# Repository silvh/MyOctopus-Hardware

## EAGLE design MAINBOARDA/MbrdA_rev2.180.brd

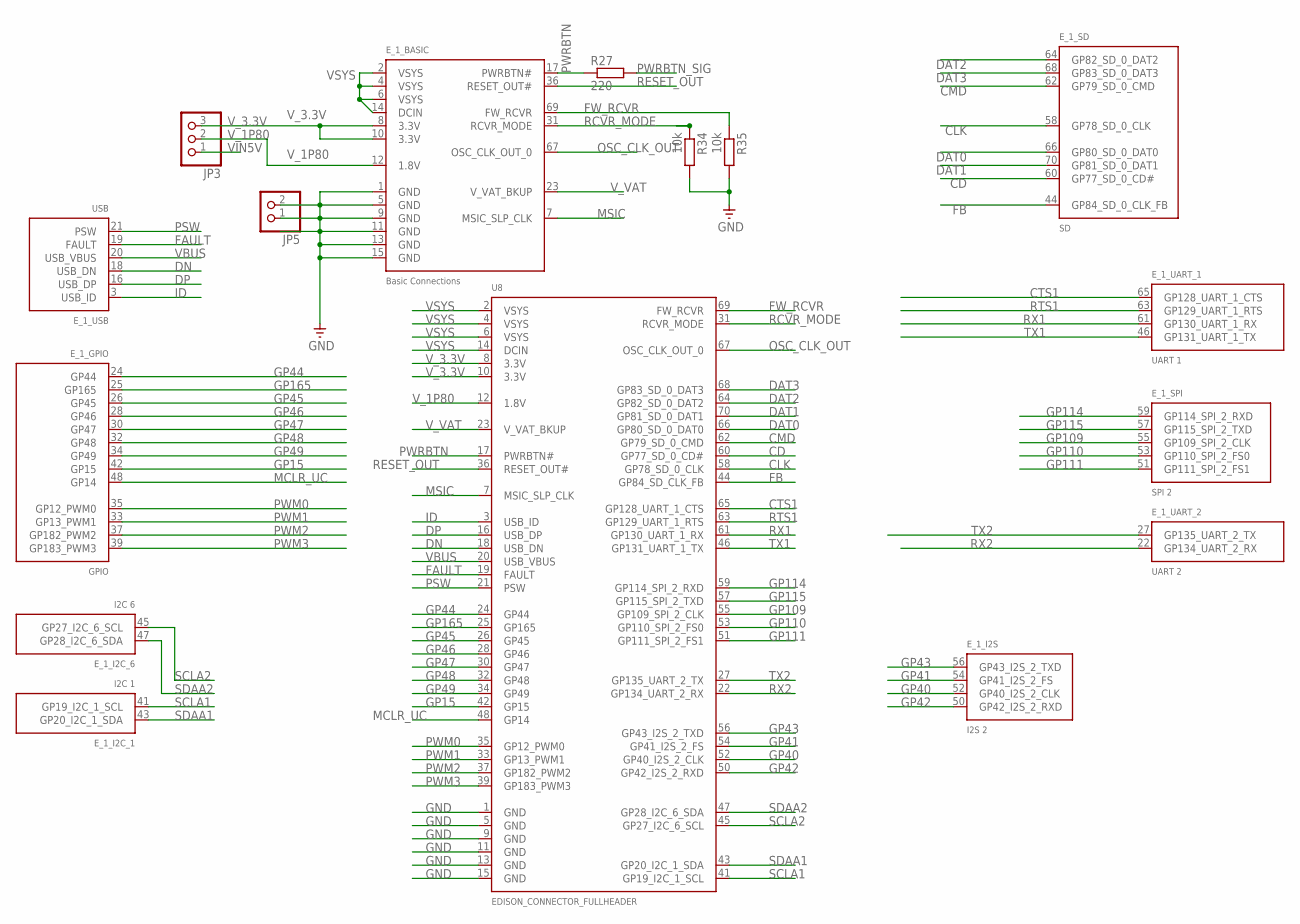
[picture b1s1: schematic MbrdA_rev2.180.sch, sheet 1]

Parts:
E_1: EDISON_CONNECTOR_SEGMENTED; EDISON_DAUGHTER; MOUSER 798-DF40HC3070DS4V51
JP3: PINHD-1X3; 1X03
JP5: PINHD-1X2; 1X02
R27: 220; R0201
R34, R35: 10k; R0201
U8: EDISON_CONNECTOR_FULLHEADER; DF40C-70DP-0.4(51)

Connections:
CD: E_1.60 (GP77_SD_0_CD#), U8.60 (GP77_SD_0_CD#); also elsewhere on the board
CLK: E_1.58 (GP78_SD_0_CLK), U8.58 (GP78_SD_0_CLK); also elsewhere on the board
CMD: E_1.62 (GP79_SD_0_CMD), U8.62 (GP79_SD_0_CMD); also elsewhere on the board
CTS1: E_1.65 (GP128_UART_1_CTS), U8.65 (GP128_UART_1_CTS); also elsewhere on the board
DAT0: E_1.66 (GP80_SD_0_DAT0), U8.66 (GP80_SD_0_DAT0); also elsewhere on the board
DAT1: E_1.70 (GP81_SD_0_DAT1), U8.70 (GP81_SD_0_DAT1); also elsewhere on the board
DAT2: E_1.64 (GP82_SD_0_DAT2), U8.64 (GP82_SD_0_DAT2); also elsewhere on the board
DAT3: E_1.68 (GP83_SD_0_DAT3), U8.68 (GP83_SD_0_DAT3); also elsewhere on the board
DN: E_1.18 (USB_DN), U8.18 (USB_DN); also elsewhere on the board
DP: E_1.16 (USB_DP), U8.16 (USB_DP); also elsewhere on the board
FAULT: E_1.19 (FAULT), U8.19 (FAULT); also elsewhere on the board
FB: E_1.44 (GP84_SD_0_CLK_FB), U8.44 (GP84_SD_CLK_FB); also elsewhere on the board
FW_RCVR: E_1.69 (FW_RCVR), R35.1, U8.69 (FW_RCVR); also elsewhere on the board
GND: E_1.1 (GND), E_1.5 (GND), E_1.9 (GND), E_1.11 (GND), E_1.13 (GND), E_1.15 (GND), JP5.1, JP5.2, R34.2, R35.2, U8.1 (GND), U8.5 (GND), U8.9 (GND), U8.11 (GND), U8.13 (GND), U8.15 (GND); also elsewhere on the board
GP15: E_1.42 (GP15), U8.42 (GP15)
GP40: E_1.52 (GP40_I2S_2_CLK), U8.52 (GP40_I2S_2_CLK)
GP41: E_1.54 (GP41_I2S_2_FS), U8.54 (GP41_I2S_2_FS)
GP42: E_1.50 (GP42_I2S_2_RXD), U8.50 (GP42_I2S_2_RXD)
GP43: E_1.56 (GP43_I2S_2_TXD), U8.56 (GP43_I2S_2_TXD)
GP44: E_1.24 (GP44), U8.24 (GP44); also elsewhere on the board
GP45: E_1.26 (GP45), U8.26 (GP45); also elsewhere on the board
GP46: E_1.28 (GP46), U8.28 (GP46); also elsewhere on the board
GP47: E_1.30 (GP47), U8.30 (GP47)
GP48: E_1.32 (GP48), U8.32 (GP48); also elsewhere on the board
GP49: E_1.34 (GP49), U8.34 (GP49); also elsewhere on the board
GP109: E_1.55 (GP109_SPI_2_CLK), U8.55 (GP109_SPI_2_CLK)
GP110: E_1.53 (GP110_SPI_2_FS0), U8.53 (GP110_SPI_2_FS0)
GP111: E_1.51 (GP111_SPI_2_FS1), U8.51 (GP111_SPI_2_FS1)
GP114: E_1.59 (GP114_SPI_2_RXD), U8.59 (GP114_SPI_2_RXD)
GP115: E_1.57 (GP115_SPI_2_TXD), U8.57 (GP115_SPI_2_TXD)
GP165: E_1.25 (GP165), U8.25 (GP165); also elsewhere on the board
ID: E_1.3 (USB_ID), U8.3 (USB_ID); also elsewhere on the board
MCLR_UC: E_1.48 (GP14), U8.48 (GP14); also elsewhere on the board
MSIC: E_1.7 (MSIC_SLP_CLK), U8.7 (MSIC_SLP_CLK)
OSC_CLK_OUT: E_1.67 (OSC_CLK_OUT_0), U8.67 (OSC_CLK_OUT_0)
PSW: E_1.21 (PSW), U8.21 (PSW); also elsewhere on the board
PWM0: E_1.35 (GP12_PWM0), U8.35 (GP12_PWM0); also elsewhere on the board
PWM1: E_1.33 (GP13_PWM1), U8.33 (GP13_PWM1); also elsewhere on the board
PWM2: E_1.37 (GP182_PWM2), U8.37 (GP182_PWM2)
PWM3: E_1.39 (GP183_PWM3), U8.39 (GP183_PWM3)
PWRBTN: E_1.17 (PWRBTN#), R27.1, U8.17 (PWRBTN#)
PWRBTN_SIG: R27.2; also elsewhere on the board
RCVR_MODE: E_1.31 (RCVR_MODE), R34.1, U8.31 (RCVR_MODE); also elsewhere on the board
RESET_OUT: E_1.36 (RESET_OUT#), U8.36 (RESET_OUT#); also elsewhere on the board
RTS1: E_1.63 (GP129_UART_1_RTS), U8.63 (GP129_UART_1_RTS); also elsewhere on the board
RX1: E_1.61 (GP130_UART_1_RX), U8.61 (GP130_UART_1_RX); also elsewhere on the board
RX2: E_1.22 (GP134_UART_2_RX), U8.22 (GP134_UART_2_RX); also elsewhere on the board
SCLA1: E_1.41 (GP19_I2C_1_SCL), U8.41 (GP19_I2C_1_SCL); also elsewhere on the board
SCLA2: E_1.45 (GP27_I2C_6_SCL), U8.45 (GP27_I2C_6_SCL); also elsewhere on the board
SDAA1: E_1.43 (GP20_I2C_1_SDA), U8.43 (GP20_I2C_1_SDA); also elsewhere on the board
SDAA2: E_1.47 (GP28_I2C_6_SDA), U8.47 (GP28_I2C_6_SDA); also elsewhere on the board
TX1: E_1.46 (GP131_UART_1_TX), U8.46 (GP131_UART_1_TX); also elsewhere on the board
TX2: E_1.27 (GP135_UART_2_TX), U8.27 (GP135_UART_2_TX); also elsewhere on the board
VBUS: E_1.20 (USB_VBUS), U8.20 (USB_VBUS); also elsewhere on the board
VIN5V: JP3.1; also elsewhere on the board
VSYS: E_1.2 (VSYS), E_1.4 (VSYS), E_1.6 (VSYS), E_1.14 (DCIN), U8.2 (VSYS), U8.4 (VSYS), U8.6 (VSYS), U8.14 (DCIN); also elsewhere on the board
V_1P80: E_1.12 (1.8V), JP3.2, U8.12 (1.8V); also elsewhere on the board
V_3.3V: E_1.8 (3.3V), E_1.10 (3.3V), JP3.3, U8.8 (3.3V), U8.10 (3.3V); also elsewhere on the board
V_VAT: E_1.23 (V_VAT_BKUP), U8.23 (V_VAT_BKUP)

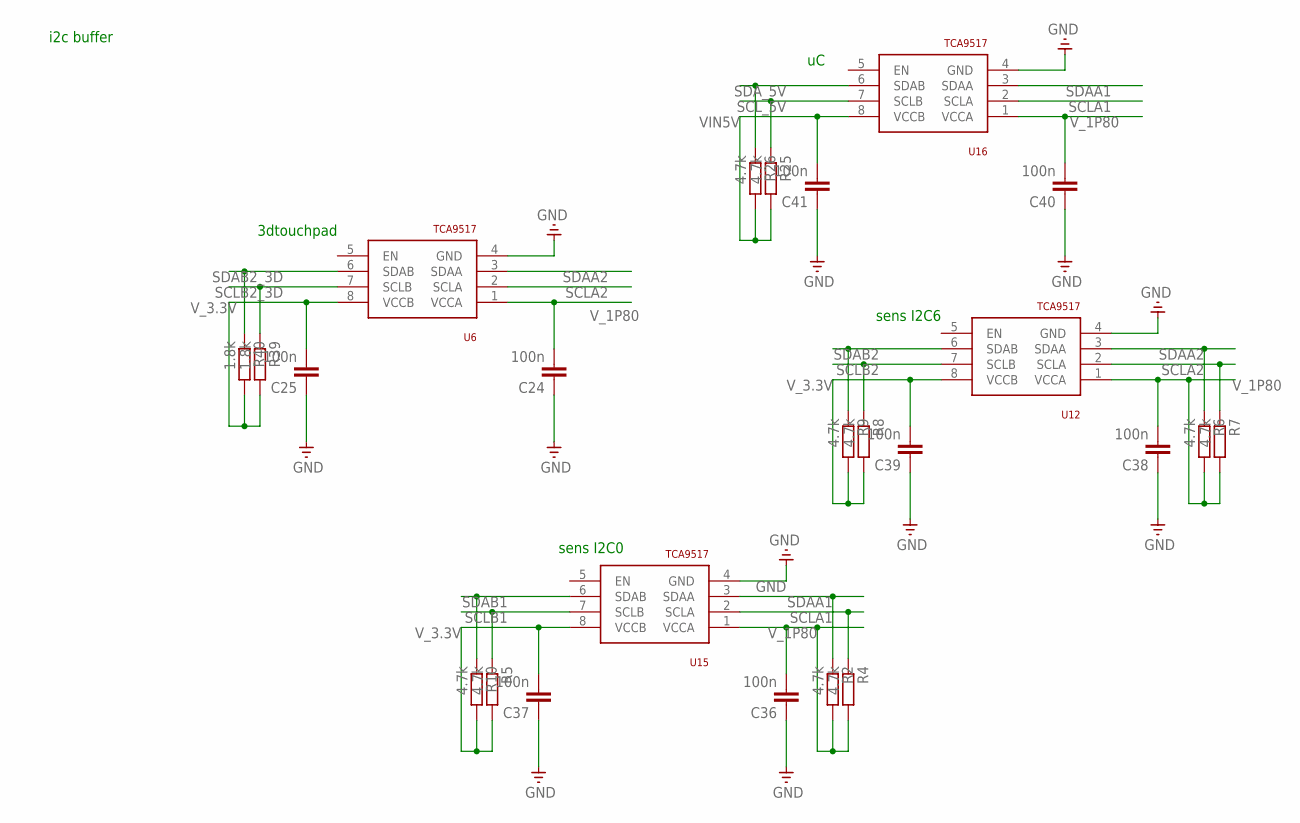
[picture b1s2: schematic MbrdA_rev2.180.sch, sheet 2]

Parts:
C24, C25, C36, C37, C38, C39, C40, C41: 100n; C0201
R2, R4, R5, R6, R7, R8, R9, R10, R25, R26: 4.7k; R0201
R39, R40: 1.8k; R0201
U6, U12, U15, U16: TCA9517; SO-08

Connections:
GND: C24.1, C25.1, C36.1, C37.1, C38.1, C39.1, C40.1, C41.1, U6.4 (GND), U12.4 (GND), U15.4 (GND), U16.4 (GND); also elsewhere on the board
SCLA1: R4.1, U15.2 (SCLA), U16.2 (SCLA); also elsewhere on the board
SCLA2: R7.1, U6.2 (SCLA), U12.2 (SCLA); also elsewhere on the board
SCLB1: R5.1, U15.7 (SCLB); also elsewhere on the board
SCLB2: R8.1, U12.7 (SCLB); also elsewhere on the board
SCLB2_3D: R39.1, U6.7 (SCLB); also elsewhere on the board
SCL_5V: R25.1, U16.7 (SCLB); also elsewhere on the board
SDAA1: R2.1, U15.3 (SDAA), U16.3 (SDAA); also elsewhere on the board
SDAA2: R6.1, U6.3 (SDAA), U12.3 (SDAA); also elsewhere on the board
SDAB1: R10.1, U15.6 (SDAB); also elsewhere on the board
SDAB2: R9.1, U12.6 (SDAB); also elsewhere on the board
SDAB2_3D: R40.1, U6.6 (SDAB); also elsewhere on the board
SDA_5V: R26.1, U16.6 (SDAB); also elsewhere on the board
VIN5V: C41.2, R25.2, R26.2, U16.8 (VCCB); also elsewhere on the board
V_1P80: C24.2, C36.2, C38.2, C40.2, R2.2, R4.2, R6.2, R7.2, U6.1 (VCCA), U12.1 (VCCA), U15.1 (VCCA), U16.1 (VCCA); also elsewhere on the board
V_3.3V: C25.2, C37.2, C39.2, R5.2, R8.2, R9.2, R10.2, R39.2, R40.2, U6.8 (VCCB), U12.8 (VCCB), U15.8 (VCCB); also elsewhere on the board

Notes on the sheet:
3dtouchpad
sens I2C0
sens I2C6
i2c buffer

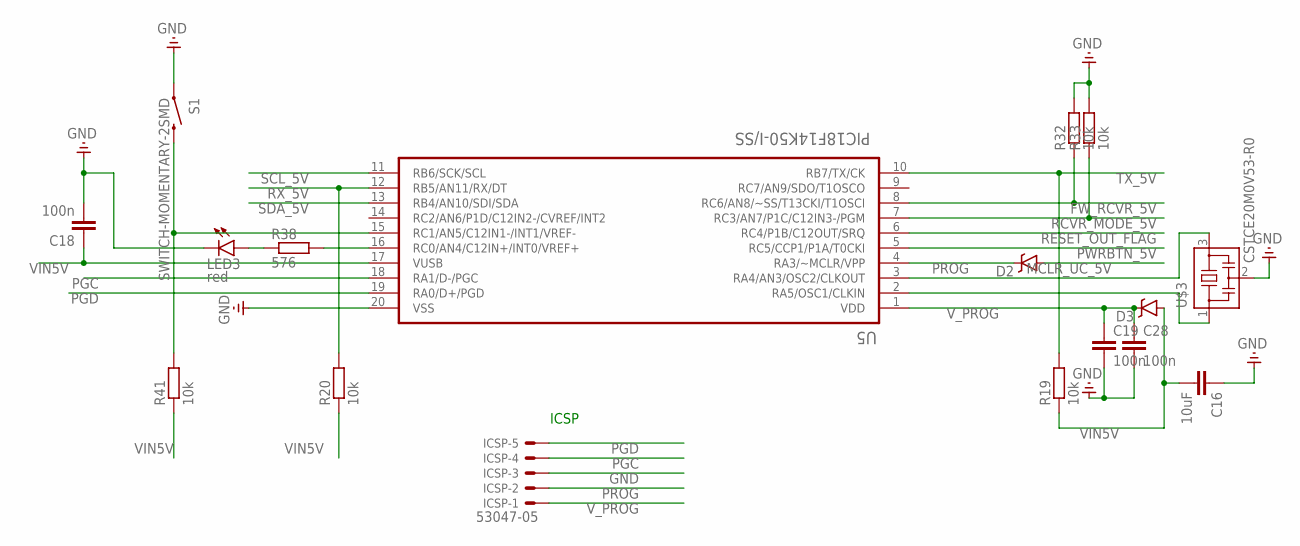
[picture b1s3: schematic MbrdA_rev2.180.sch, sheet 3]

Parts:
C16: 10uF; C0402
C18, C19, C28: 100n; C0201
D2, D3: DB2W31900L; MINI-F3-B
ICSP: 53047-05
LED3: red; LED0402
R19, R20, R32, R33, R41: 10k; R0201
R38: 576; R0201
S1: SWITCH-MOMENTARY-2SMD; TACTILE_SWITCH_SMD
U5: PIC18F14K50-I/SS; SOP65P780X200-20N
U$3: CSTCE20M0V53-R0; CSTER12M

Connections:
FW_RCVR_5V: R32.1, U5.8 (RC6/AN8/~SS/T13CKI/T1OSCI); also elsewhere on the board
GND: C16.1, C18.2, C19.2, C28.2, ICSP.3, LED3.C, R32.2, R33.2, S1.1, U5.20 (VSS), U$3.2; also elsewhere on the board
MCLR_UC_5V: D2.A; also elsewhere on the board
unnamed: LED3.A, R38.1
unnamed: R38.2, U5.16 (RC0/AN4/C12IN+/INT0/VREF+)
unnamed: R41.2, S1.3 (2), U5.15 (RC1/AN5/C12IN1-/INT1/VREF-)
unnamed: U5.2 (RA5/OSC1/CLKIN), U$3.1
unnamed: U5.3 (RA4/AN3/OSC2/CLKOUT), U$3.3
PGC: ICSP.4, U5.18 (RA1/D-/PGC)
PGD: ICSP.5, U5.19 (RA0/D+/PGD)
PROG: D2.C, ICSP.2, U5.4 (RA3/~MCLR/VPP)
PWRBTN_5V: U5.5 (RC5/CCP1/P1A/T0CKI); also elsewhere on the board
RCVR_MODE_5V: R33.1, U5.7 (RC3/AN7/P1C/C12IN3-/PGM); also elsewhere on the board
RESET_OUT_FLAG: U5.6 (RC4/P1B/C12OUT/SRQ); also elsewhere on the board
RX_5V: R20.2, U5.12 (RB5/AN11/RX/DT); also elsewhere on the board
SCL_5V: U5.11 (RB6/SCK/SCL); also elsewhere on the board
SDA_5V: U5.13 (RB4/AN10/SDI/SDA); also elsewhere on the board
TX_5V: R19.2, U5.10 (RB7/TX/CK); also elsewhere on the board
VIN5V: C16.2, C18.1, D3.A, R19.1, R20.1, R41.1, U5.17 (VUSB); also elsewhere on the board
V_PROG: C19.1, C28.1, D3.C, ICSP.1, U5.1 (VDD)

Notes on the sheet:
ICSP

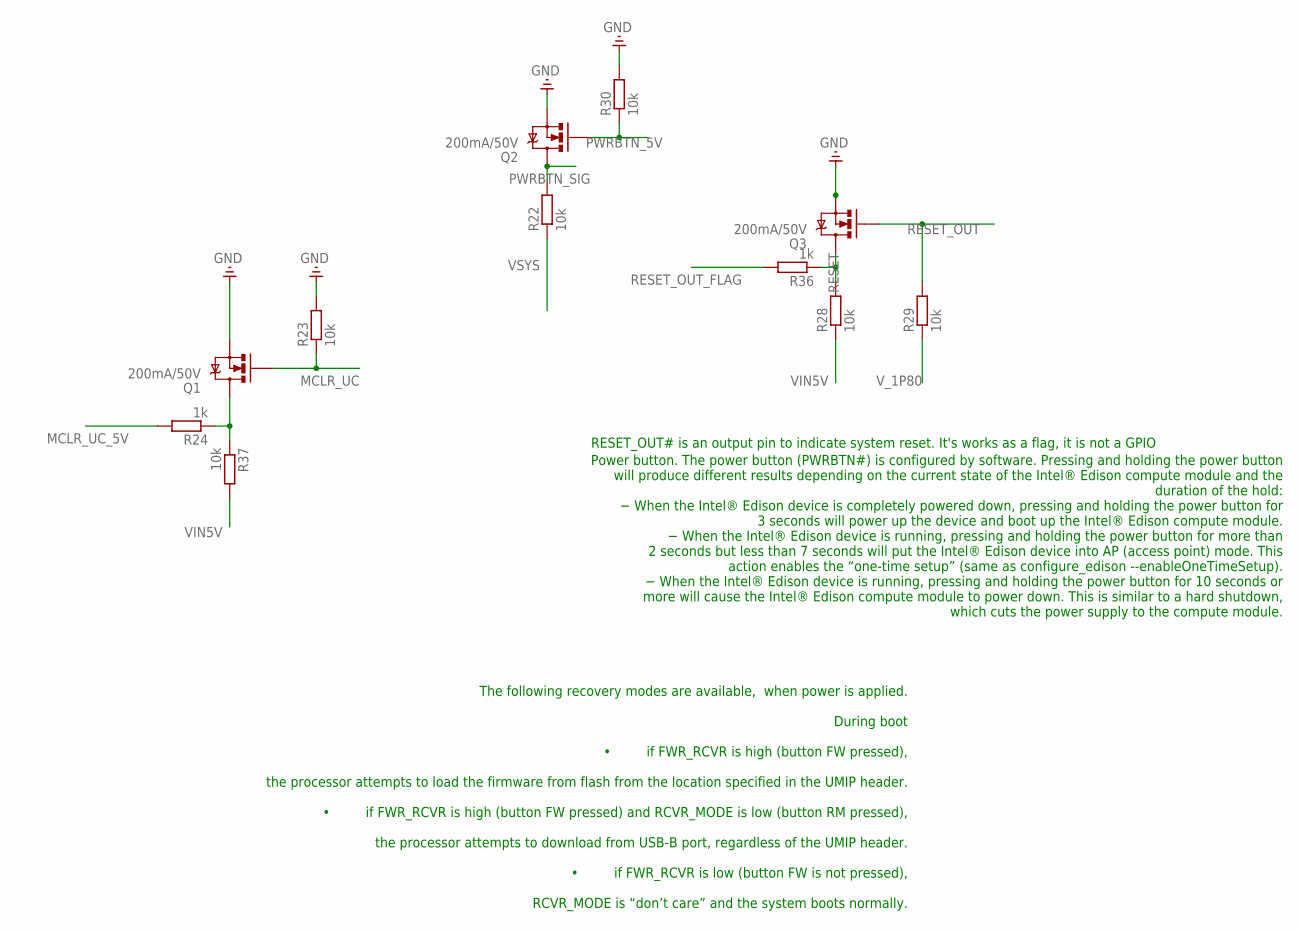
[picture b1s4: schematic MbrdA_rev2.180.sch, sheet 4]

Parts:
Q1, Q2, Q3: 200mA/50V; SOT23-3
R22, R23, R28, R29, R30, R37: 10k; R0201
R24, R36: 1k; R0201

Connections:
GND: Q1.2 (S), Q2.2 (S), Q3.2 (S), R23.2, R30.2; also elsewhere on the board
MCLR_UC: Q1.1 (G), R23.1; also elsewhere on the board
MCLR_UC_5V: R24.2; also elsewhere on the board
unnamed: Q1.3 (D), R24.1, R37.1
PWRBTN_5V: Q2.1 (G), R30.1; also elsewhere on the board
PWRBTN_SIG: Q2.3 (D), R22.2; also elsewhere on the board
RESET: Q3.3 (D), R28.2, R36.1
RESET_OUT: Q3.1 (G), R29.2; also elsewhere on the board
RESET_OUT_FLAG: R36.2; also elsewhere on the board
VIN5V: R28.1, R37.2; also elsewhere on the board
VSYS: R22.1; also elsewhere on the board
V_1P80: R29.1; also elsewhere on the board

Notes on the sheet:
RESET_OUT# is an output pin to indicate system reset. It's works as a flag, it is not a GPIO
Power button. The power button (PWRBTN#) is configured by software. Pressing and holding the power button will produce different results depending on the current state of the Intel® Edison compute module and the duration of the hold: − When the Intel® Edison device is completely powered down, press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
The following recovery modes are available, when power is applied. During boot • if FWR_RCVR is high (button FW pressed), the processor attempts to load the firmware from flash from the location specified in the UMIP header. • if FWR_RCVR is high (button FW pressed) and RCVR_MODE is low (button RM 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

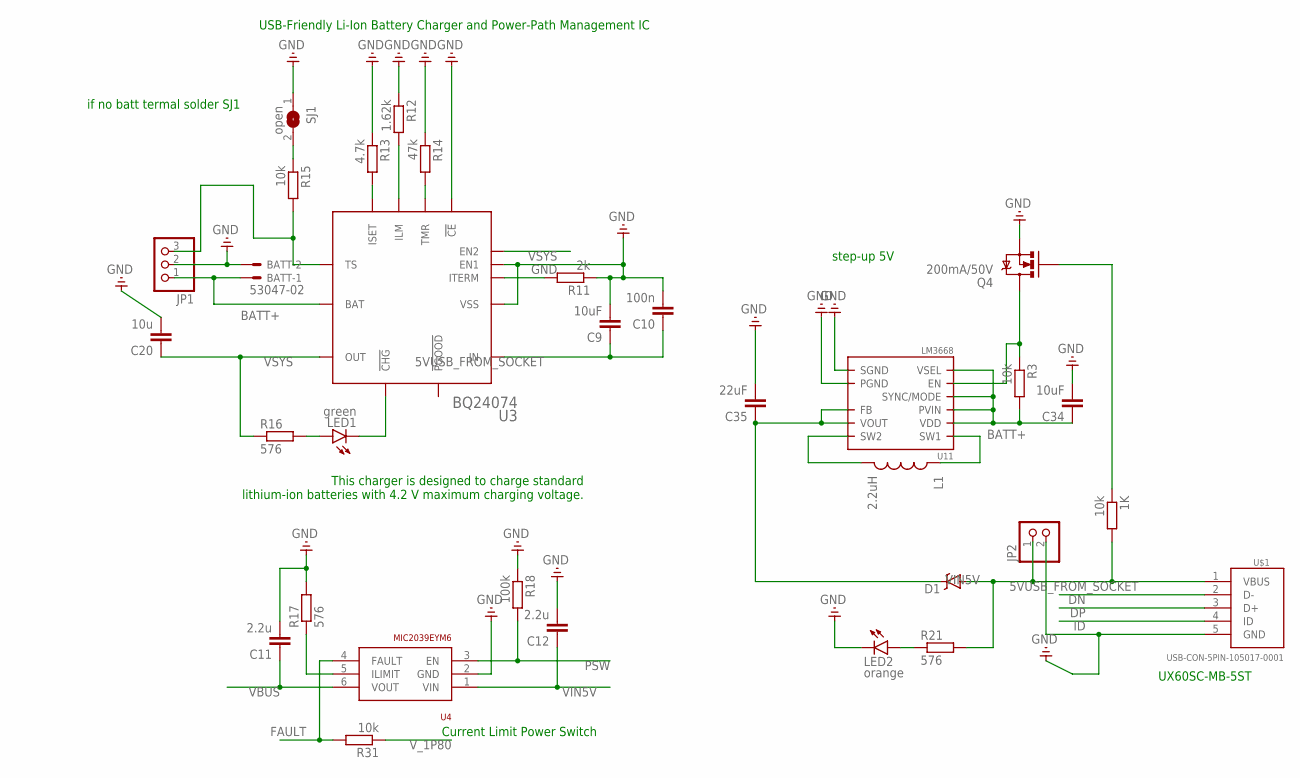
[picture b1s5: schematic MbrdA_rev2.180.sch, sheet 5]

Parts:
1K: 10k; R0201
BATT: 53047-02
C9: 10uF; C0402
C10: 100n; C0201
C11, C12: 2.2u; C0603
C20: 10u; C0402
C34: 10uF; C0805
C35: 22uF; C0805
D1: DB2W31900L; MINI-F3-B
JP1: PINHD-1X3; 1X03
JP2: PINHD-1X2; 1X02
L1: 2.2uH; LPS4018
LED1: green; LED0402
LED2: orange; LED0402
Q4: 200mA/50V; SOT23-3
R3, R15, R31: 10k; R0201
R11: 2k; R0201
R12: 1.62k; R0201
R13: 4.7k; R0201
R14: 47k; R0201
R16, R17, R21: 576; R0201
R18: 100k; R0201
SJ1: open; SJ
U3: BQ24074; QFN-16_BOT_PAD
U4: MIC2039EYM6; SOT23-6L
U11: LM3668; LLP.12.3X3MM
U$1: USB-CON-5PIN-105017-0001; USB-MICRO-MOLEX-105017-0001

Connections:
5VUSB_FROM_SOCKET: 1K.2, C9.1, C10.1, D1.A, JP2.1, R21.2, U3.13 (IN), U$1.1 (VBUS)
BATT+: BATT.1, C34.1, JP1.1, R3.2, U3.2 (BAT), U3.3 (BAT), U11.5 (PVIN), U11.7 (VDD), U11.10 (SYNC/MODE), U11.11 (VSEL)
DN: U$1.2 (D-); also elsewhere on the board
DP: U$1.3 (D+); also elsewhere on the board
FAULT: R31.2, U4.4 (FAULT); also elsewhere on the board
GND: BATT.2, C9.2, C10.2, C11.2, C12.2, C20.2, C34.2, C35.2, JP1.2, JP2.2, LED2.C, Q4.2 (S), R11.1, R12.1, R13.1, R14.1, R17.2, R18.1, SJ1.1, U3.4 (!CE), U3.6 (EN1), U3.8 (VSS), U3.PAD0 (VSS), U3.PAD1 (VSS), U4.2 (GND), U11.3 (PGND), U11.8 (SGND), U11.9 (SGND), U11.PAD (SGND), U$1.5 (GND); also elsewhere on the board
ID: U$1.4 (ID); also elsewhere on the board
unnamed: R11.2, U3.15 (ITERM)
unnamed: LED1.C, U3.9 (!CHG)
unnamed: R13.2, U3.16 (ISET)
unnamed: R12.2, U3.12 (ILM)
unnamed: R14.2, U3.14 (TMR)
unnamed: 1K.1, Q4.1 (G)
unnamed: LED1.A, R16.2
unnamed: JP1.3, R15.2, U3.1 (TS)
unnamed: R17.1, U4.5 (ILIMIT)
unnamed: Q4.3 (D), R3.1, U11.6 (EN)
unnamed: L1.2, U11.2 (SW2)
unnamed: LED2.A, R21.1
unnamed: L1.1, U11.4 (SW1)
unnamed: R15.1, SJ1.2
PSW: R18.2, U4.3 (EN); also elsewhere on the board
VBUS: C11.1, U4.6 (VOUT); also elsewhere on the board
VIN5V: C12.1, C35.1, D1.C, U4.1 (VIN), U11.1 (VOUT), U11.12 (FB); also elsewhere on the board
VSYS: C20.1, R16.1, U3.5 (EN2), U3.10 (OUT), U3.11 (OUT); also elsewhere on the board
V_1P80: R31.1; also elsewhere on the board

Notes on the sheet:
UX60SC-MB-5ST
Current Limit Power Switch
USB-Friendly Li-Ion Battery Charger and Power-Path Management IC
This charger is designed to charge standard lithium-ion batteries with 4.2 V maximum charging voltage.
if no batt termal solder SJ1
step-up 5V

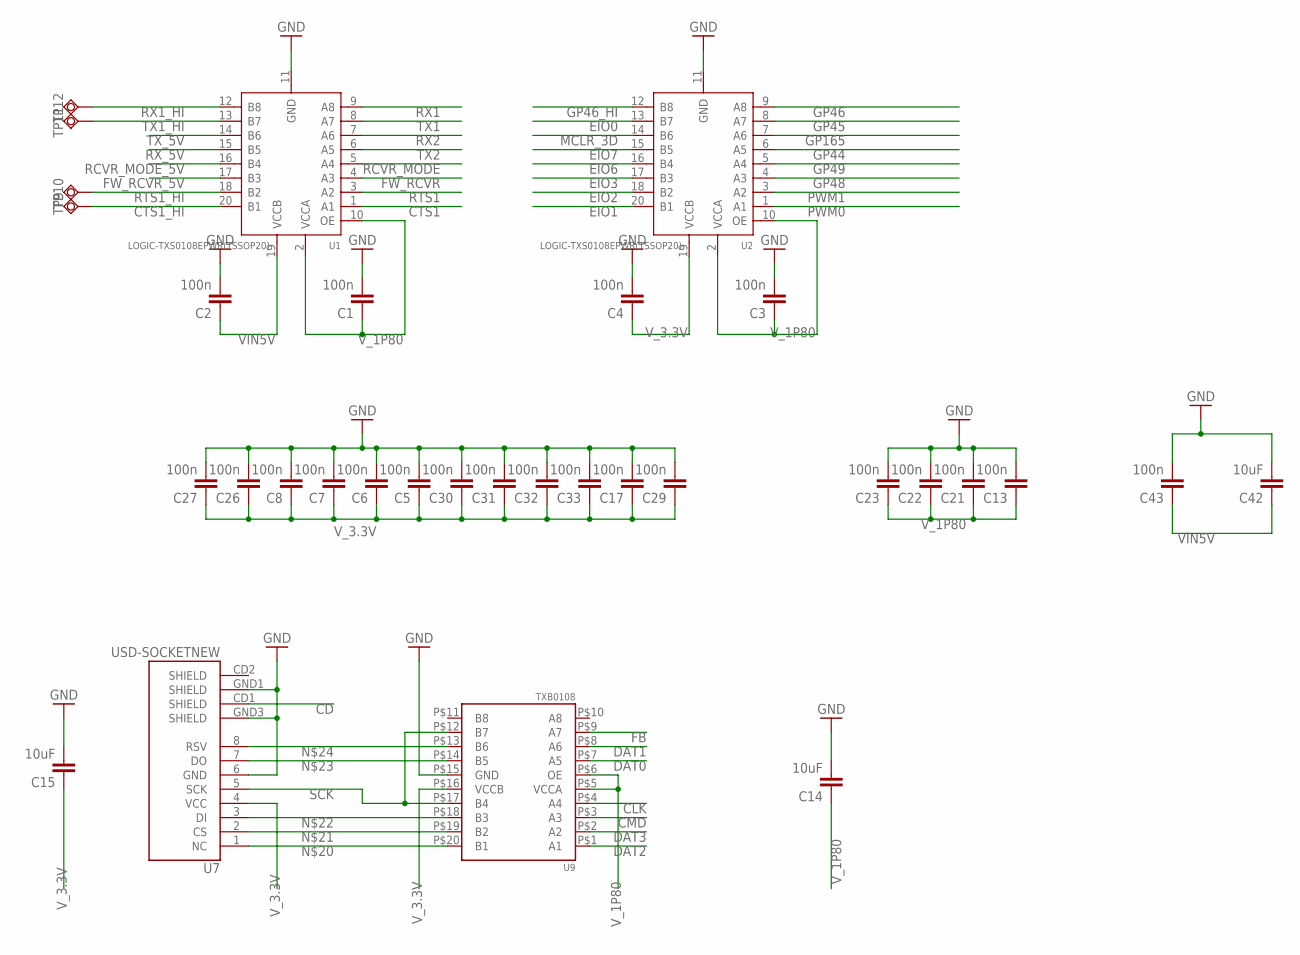
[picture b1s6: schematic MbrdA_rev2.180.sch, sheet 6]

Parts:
C1, C2, C3, C4, C5, C6, C7, C8, C13, C17, C21, C22, C23, C26, C27, C29, C30, C31, C32, C33, C43: 100n; C0201
C14, C15: 10uF; C0402
C42: 10uF; C0805
TP9, TP10, TP11, TP12: TPSQPAD1-13; P1-13
U1, U2: LOGIC-TXS0108EPWR(TSSOP20); TSSOP20-0.65-6.5X4.4MM
U7: USD-SOCKETNEW; MICRO-SD-SOCKET-PP
U9: TXB0108; UFDFN-20

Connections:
CD: U7.CD1 (SHIELD); also elsewhere on the board
CLK: U9.P$4 (A4); also elsewhere on the board
CMD: U9.P$3 (A3); also elsewhere on the board
CTS1: U1.1 (A1); also elsewhere on the board
CTS1_HI: TP9.TP, U1.20 (B1)
DAT0: U9.P$7 (A5); also elsewhere on the board
DAT1: U9.P$8 (A6); also elsewhere on the board
DAT2: U9.P$1 (A1); also elsewhere on the board
DAT3: U9.P$2 (A2); also elsewhere on the board
EIO0: U2.13 (B7); also elsewhere on the board
EIO1: U2.20 (B1); also elsewhere on the board
EIO2: U2.18 (B2); also elsewhere on the board
EIO3: U2.17 (B3); also elsewhere on the board
EIO6: U2.16 (B4); also elsewhere on the board
EIO7: U2.15 (B5); also elsewhere on the board
FB: U9.P$9 (A7); also elsewhere on the board
FW_RCVR: U1.4 (A3); also elsewhere on the board
FW_RCVR_5V: U1.17 (B3); also elsewhere on the board
GND: C1.2, C2.2, C3.2, C4.2, C5.2, C6.2, C7.2, C8.2, C13.2, C14.2, C15.2, C17.2, C21.2, C22.2, C23.2, C26.2, C27.2, C29.2, C30.2, C31.2, C32.2, C33.2, C42.2, C43.2, U1.11 (GND), U2.11 (GND), U7.6 (GND), U7.GND1 (SHIELD), U7.GND3 (SHIELD), U9.P$15 (GND); also elsewhere on the board
GP44: U2.6 (A5); also elsewhere on the board
GP45: U2.8 (A7); also elsewhere on the board
GP46: U2.9 (A8); also elsewhere on the board
GP46_HI: U2.12 (B8); also elsewhere on the board
GP48: U2.4 (A3); also elsewhere on the board
GP49: U2.5 (A4); also elsewhere on the board
GP165: U2.7 (A6); also elsewhere on the board
MCLR_3D: U2.14 (B6); also elsewhere on the board
unnamed: U7.1 (NC), U9.P$20 (B1)
unnamed: U7.2 (CS), U9.P$19 (B2)
unnamed: U7.3 (DI), U9.P$18 (B3)
unnamed: U7.7 (DO), U9.P$14 (B5)
unnamed: U7.8 (RSV), U9.P$13 (B6)
PWM0: U2.1 (A1); also elsewhere on the board
PWM1: U2.3 (A2); also elsewhere on the board
RCVR_MODE: U1.5 (A4); also elsewhere on the board
RCVR_MODE_5V: U1.16 (B4); also elsewhere on the board
RTS1: U1.3 (A2); also elsewhere on the board
RTS1_HI: TP10.TP, U1.18 (B2)
RX1: U1.9 (A8); also elsewhere on the board
RX1_HI: TP12.TP, U1.12 (B8)
RX2: U1.7 (A6); also elsewhere on the board
RX_5V: U1.15 (B5); also elsewhere on the board
SCK: U7.5 (SCK), U9.P$12 (B7), U9.P$17 (B4)
TX1: U1.8 (A7); also elsewhere on the board
TX1_HI: TP11.TP, U1.13 (B7)
TX2: U1.6 (A5); also elsewhere on the board
TX_5V: U1.14 (B6); also elsewhere on the board
VIN5V: C2.1, C42.1, C43.1, U1.19 (VCCB); also elsewhere on the board
V_1P80: C1.1, C3.1, C13.1, C14.1, C21.1, C22.1, C23.1, U1.2 (VCCA), U1.10 (OE), U2.2 (VCCA), U2.10 (OE), U9.P$5 (VCCA), U9.P$6 (OE); also elsewhere on the board
V_3.3V: C4.1, C5.1, C6.1, C7.1, C8.1, C15.1, C17.1, C26.1, C27.1, C29.1, C30.1, C31.1, C32.1, C33.1, U2.19 (VCCB), U7.4 (VCC), U9.P$16 (VCCB); also elsewhere on the board

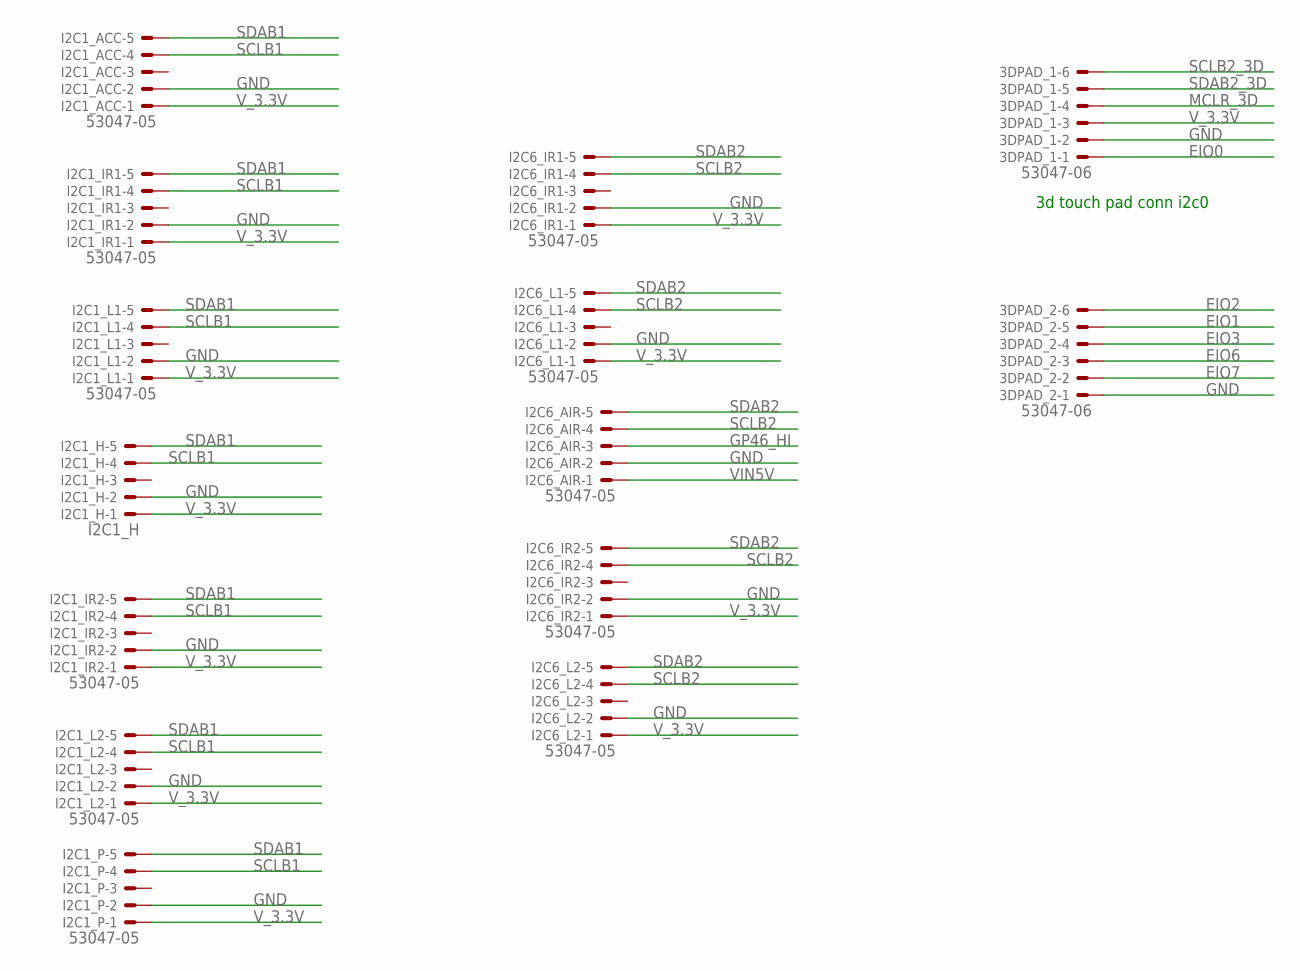
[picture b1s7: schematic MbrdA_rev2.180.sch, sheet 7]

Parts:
3DPAD_1, 3DPAD_2: 53047-06
I2C1_ACC, I2C1_IR1, I2C1_IR2, I2C1_L1, I2C1_L2, I2C1_P, I2C6_AIR, I2C6_IR1, I2C6_IR2, I2C6_L1, I2C6_L2: 53047-05
I2C1_H: I2C1_H; 53047-05

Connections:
EIO0: 3DPAD_1.1; also elsewhere on the board
EIO1: 3DPAD_2.5; also elsewhere on the board
EIO2: 3DPAD_2.6; also elsewhere on the board
EIO3: 3DPAD_2.4; also elsewhere on the board
EIO6: 3DPAD_2.3; also elsewhere on the board
EIO7: 3DPAD_2.2; also elsewhere on the board
GND: 3DPAD_1.2, 3DPAD_2.1, I2C1_ACC.2, I2C1_H.2, I2C1_IR1.2, I2C1_IR2.2, I2C1_L1.2, I2C1_L2.2, I2C1_P.2, I2C6_AIR.2, I2C6_IR1.2, I2C6_IR2.2, I2C6_L1.2, I2C6_L2.2; also elsewhere on the board
GP46_HI: I2C6_AIR.3; also elsewhere on the board
MCLR_3D: 3DPAD_1.4; also elsewhere on the board
SCLB1: I2C1_ACC.4, I2C1_H.4, I2C1_IR1.4, I2C1_IR2.4, I2C1_L1.4, I2C1_L2.4, I2C1_P.4; also elsewhere on the board
SCLB2: I2C6_AIR.4, I2C6_IR1.4, I2C6_IR2.4, I2C6_L1.4, I2C6_L2.4; also elsewhere on the board
SCLB2_3D: 3DPAD_1.6; also elsewhere on the board
SDAB1: I2C1_ACC.5, I2C1_H.5, I2C1_IR1.5, I2C1_IR2.5, I2C1_L1.5, I2C1_L2.5, I2C1_P.5; also elsewhere on the board
SDAB2: I2C6_AIR.5, I2C6_IR1.5, I2C6_IR2.5, I2C6_L1.5, I2C6_L2.5; also elsewhere on the board
SDAB2_3D: 3DPAD_1.5; also elsewhere on the board
VIN5V: I2C6_AIR.1; also elsewhere on the board
V_3.3V: 3DPAD_1.3, I2C1_ACC.1, I2C1_H.1, I2C1_IR1.1, I2C1_IR2.1, I2C1_L1.1, I2C1_L2.1, I2C1_P.1, I2C6_IR1.1, I2C6_IR2.1, I2C6_L1.1, I2C6_L2.1; also elsewhere on the board

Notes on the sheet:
3d touch pad conn i2c0

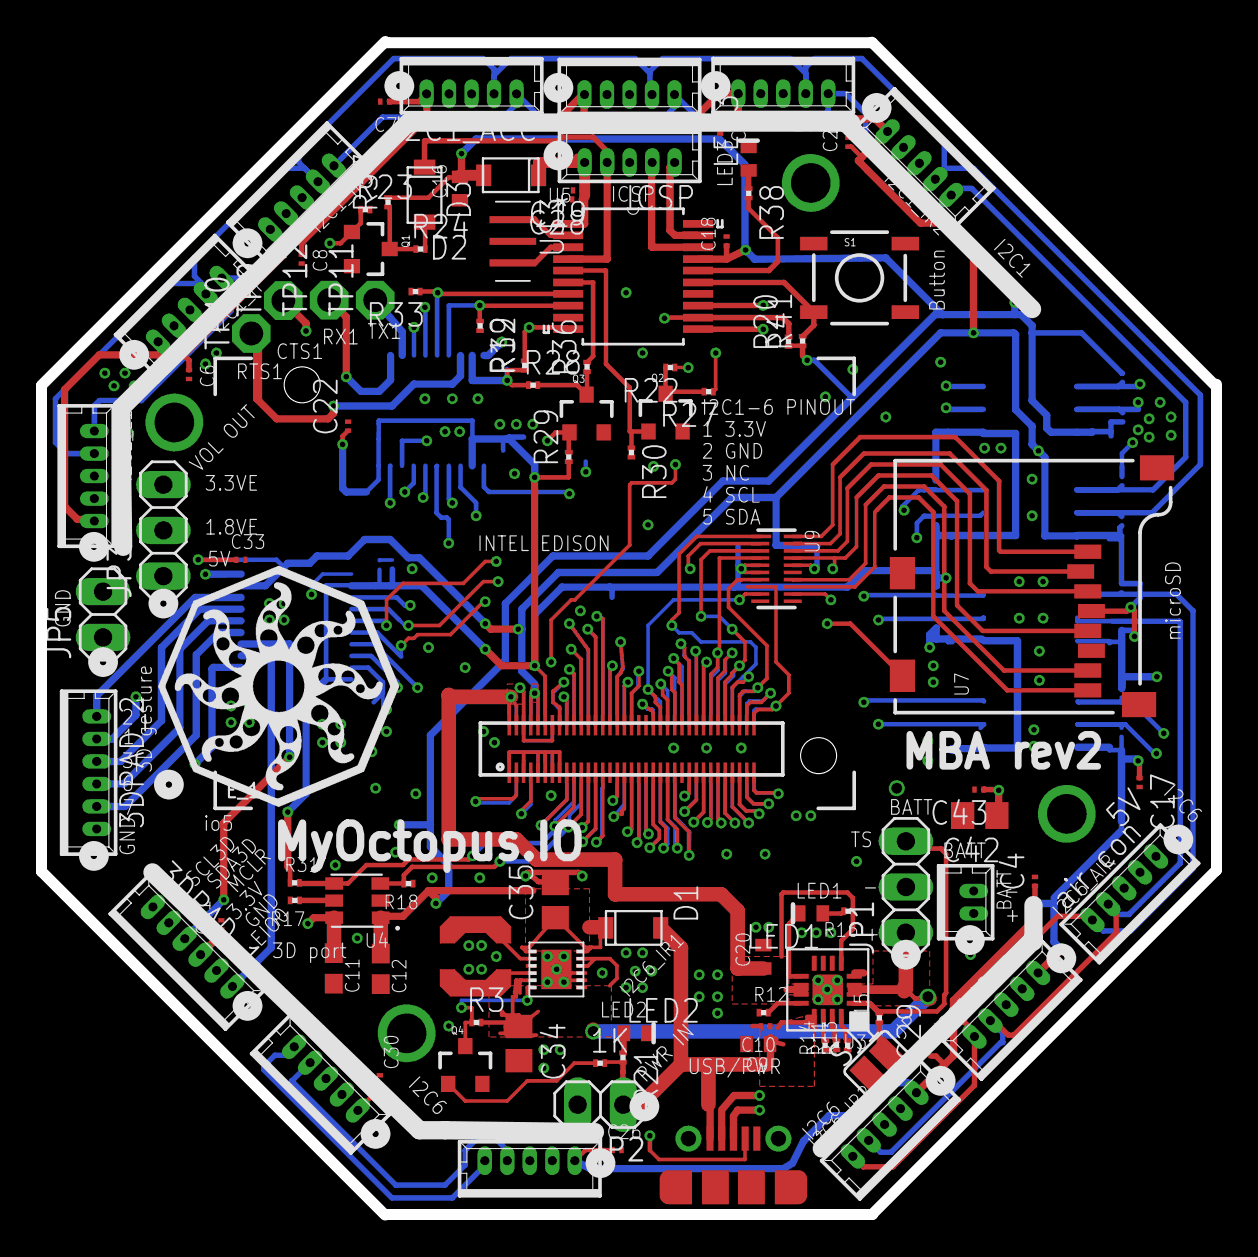
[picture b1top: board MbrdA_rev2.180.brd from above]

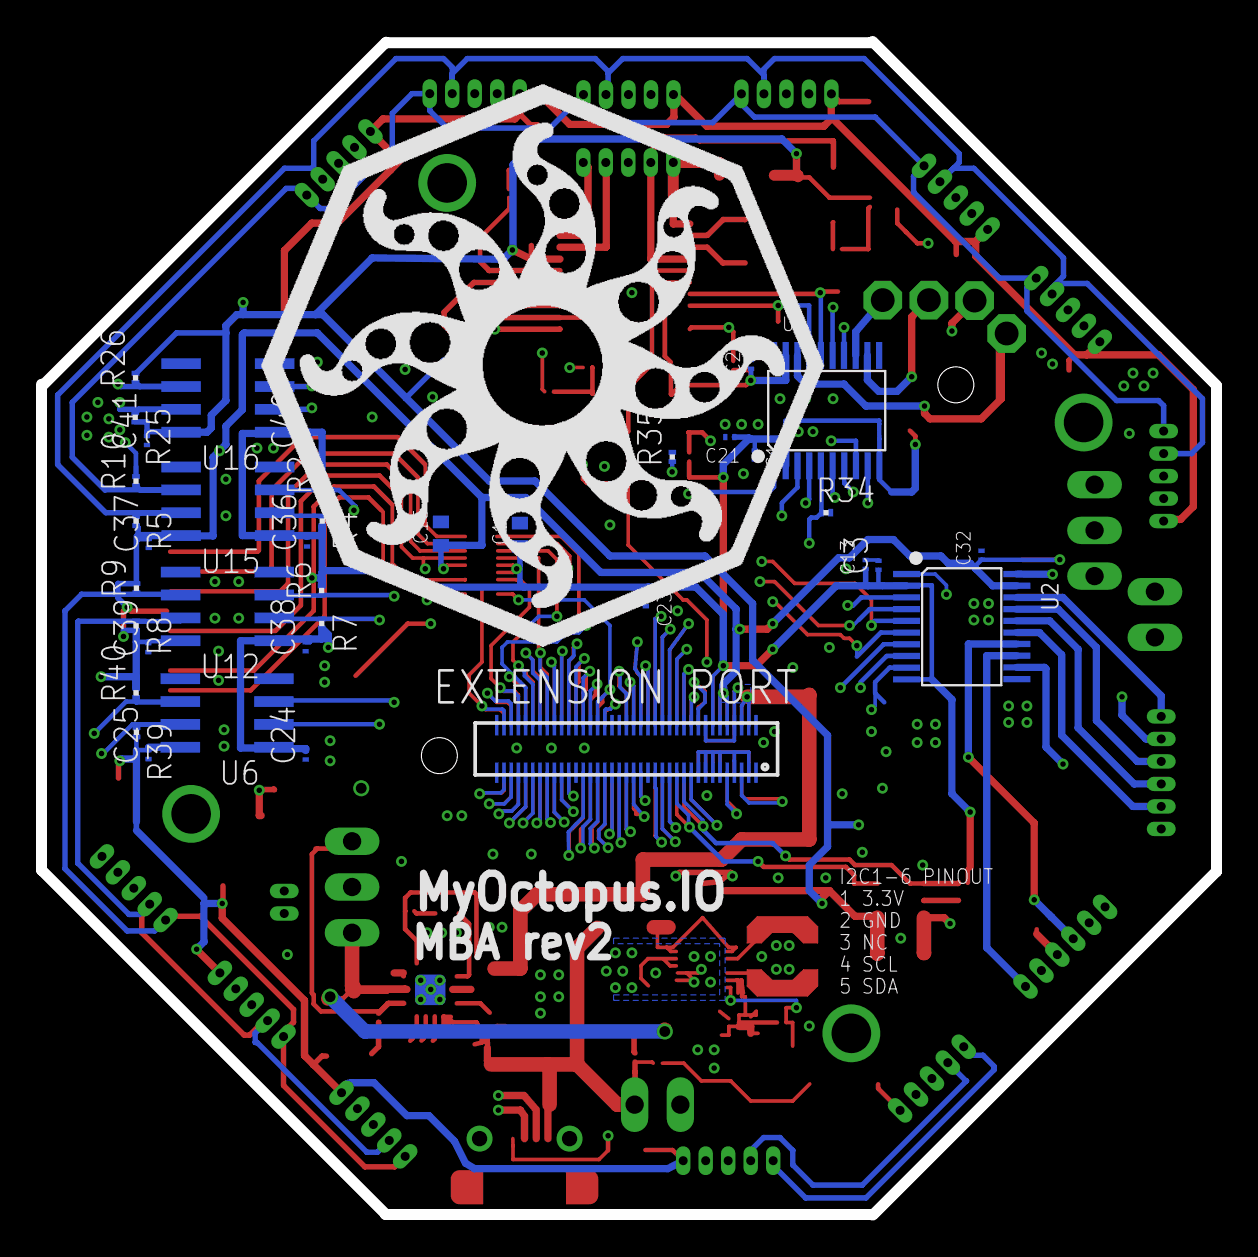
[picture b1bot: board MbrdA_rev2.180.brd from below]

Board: 4 copper layers, 65.3 x 65.2 mm, 137 parts (37 on the bottom side), 119 nets.

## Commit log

2016-12-09 add files
2016-12-09 del dir

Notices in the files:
parts and their libraries:
SparkFun-DiscreteSemi: Licensing: Creative Commons ShareAlike 4.0 International - https://creativecommons.org/licenses/by-sa/4.0
